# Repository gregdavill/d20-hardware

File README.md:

# d20-hardware
Hardware design files for the icosahedron d20 build.

Read the blog post to read more about the project: https://gregdavill.com/blog/d20

## Assembly BOM
 - 1x d20-control PCBA
 - 20x d20-tri PCBA
 - 20x 6P 0.5mm FFC, 50mm length, opposite side
 - 1x d20_enclosure_r0.1_001.stl
 - 1x d20_enclosure_r0.1_002.stl
 - 1x Sony NP-FW50 battery (knock-offs work fine)

## PCBs

Please use version r0.3 of the d20-tri boards, the earlier versions have severe errata.

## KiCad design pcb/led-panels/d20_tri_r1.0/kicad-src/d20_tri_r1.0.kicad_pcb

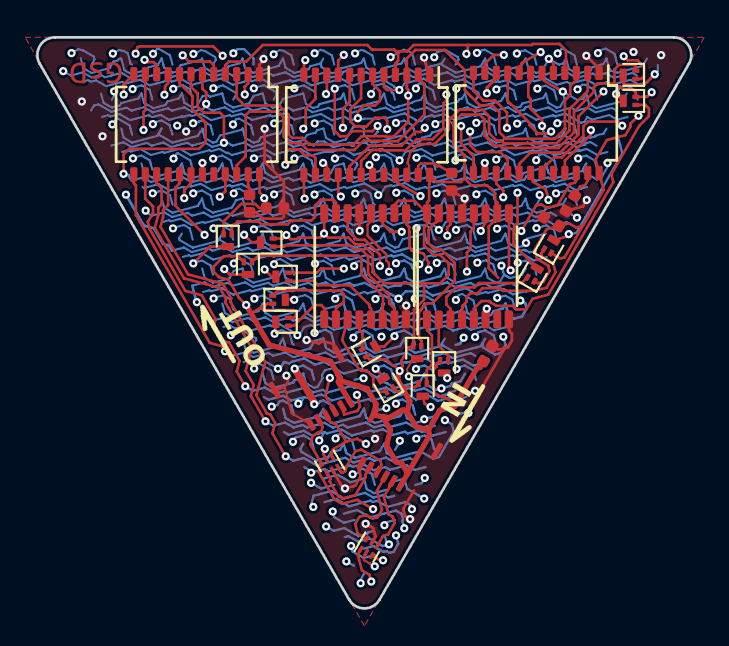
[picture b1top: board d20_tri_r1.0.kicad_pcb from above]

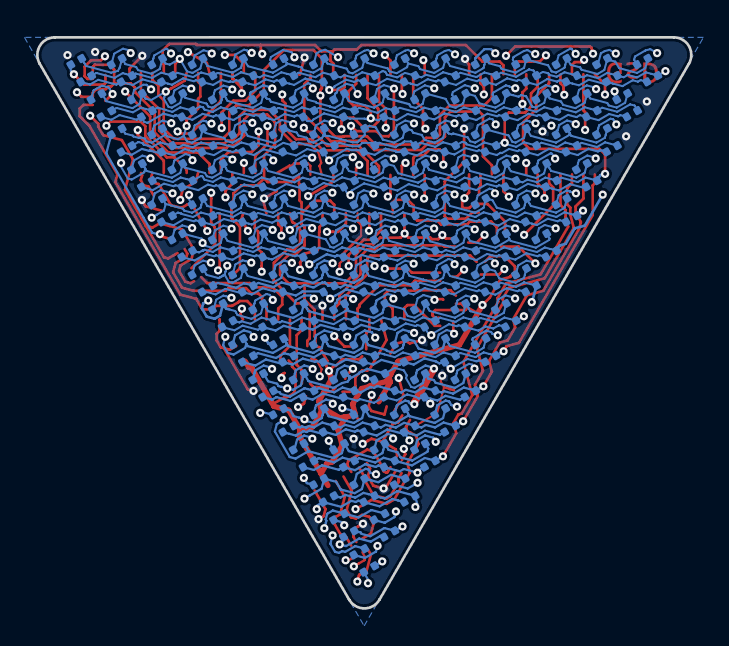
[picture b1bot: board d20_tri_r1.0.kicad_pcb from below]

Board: 4 copper layers, 36.3 x 31.7 mm, 150 parts (120 on the bottom side), 93 nets.

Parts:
C1, C2, C3: 100nF; C_0402_1005Metric
D1, D2, D3, D4, D5, D6, D7, D8, D9, D10, D11, D12, D13, D14, D15, D17, D18, D19, D20, D21, D22, D23, D24, D25, D26, D27, D28, D29, D30, D33, D34, D35, D36, D37, D38, D39, D40, D41, D42, D43, D44, D45, D49, D50, D51, D52, D53, D54, D55, D56, D57, D58, D59, D60, D65, D66, D67, D68, D69, D70, D71, D72, D73, D74, D75, D81, D82, D83, D84, D85, D86, D87, D88, D89, D90, D97, D98, D99, D100, D101, D102, D103, D104, D105, D113, D114, D115, D116, D117, D118, D119, D120, D129, D130, D131, D132, D133, D134, D135, D145, D146, D147, D148, D149, D150, D161, D162, D163, D164, D165, D177, D178, D179, D180, D193, D194, D195, D209, D210, D225: LED_ARGB; led_rbag_1515
J1: input; 5034800600
J2: output; 5034800600
Q1, Q2, Q3, Q4, Q5, Q6, Q7, Q8, Q9, Q10, Q11, Q12, Q13, Q14, Q15: LP0404N3T5G; SOT-883
R1: 2.2k; R_0402_1005Metric
R2: 7.5k; R_0402_1005Metric
R3: 4.12k; R_0402_1005Metric
U1, U2, U3: TLC59025; SSOP-24_slim
U4, U5: 74HC595; TSSOP-16_slim
U6, U7: NC7WZ17; UDFN-6_1x1mm_P0.35mm

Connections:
U1_r_ext: R1.1, U1.23
U2_r_ext: R2.1, U2.23
U3_r_ext: R3.1, U3.23
blank: J2.3, U1.21, U2.21, U3.21, U6.4
blank_i: J1.3, U6.3
colb_0: D1.2, D17.2, D33.2, D49.2, D65.2, D81.2, D97.2, D113.2, D129.2, D145.2, D161.2, D177.2, D193.2, D209.2, D225.2, U3.5
colb_1: D2.2, D18.2, D34.2, D50.2, D66.2, D82.2, D98.2, D114.2, D130.2, D146.2, D162.2, D178.2, D194.2, D210.2, U3.6
colb_2: D3.2, D19.2, D35.2, D51.2, D67.2, D83.2, D99.2, D115.2, D131.2, D147.2, D163.2, D179.2, D195.2, U3.7
colb_3: D4.2, D20.2, D36.2, D52.2, D68.2, D84.2, D100.2, D116.2, D132.2, D148.2, D164.2, D180.2, U3.8
colb_4: D5.2, D21.2, D37.2, D53.2, D69.2, D85.2, D101.2, D117.2, D133.2, D149.2, D165.2, U3.9
colb_5: D6.2, D22.2, D38.2, D54.2, D70.2, D86.2, D102.2, D118.2, D134.2, D150.2, U3.10
colb_6: D7.2, D23.2, D39.2, D55.2, D71.2, D87.2, D103.2, D119.2, D135.2, U3.11
colb_7: D8.2, D24.2, D40.2, D56.2, D72.2, D88.2, D104.2, D120.2, U3.12
colb_8: D9.2, D25.2, D41.2, D57.2, D73.2, D89.2, D105.2, U3.13
colb_9: D10.2, D26.2, D42.2, D58.2, D74.2, D90.2, U3.14
colb_10: D11.2, D27.2, D43.2, D59.2, D75.2, U3.15
colb_11: D12.2, D28.2, D44.2, D60.2, U3.16
colb_12: D13.2, D29.2, D45.2, U3.17
colb_13: D14.2, D30.2, U3.18
colb_14: D15.2, U3.19
colg_0: D1.3, D17.3, D33.3, D49.3, D65.3, D81.3, D97.3, D113.3, D129.3, D145.3, D161.3, D177.3, D193.3, D209.3, D225.3, U2.5
colg_1: D2.3, D18.3, D34.3, D50.3, D66.3, D82.3, D98.3, D114.3, D130.3, D146.3, D162.3, D178.3, D194.3, D210.3, U2.6
colg_2: D3.3, D19.3, D35.3, D51.3, D67.3, D83.3, D99.3, D115.3, D131.3, D147.3, D163.3, D179.3, D195.3, U2.7
colg_3: D4.3, D20.3, D36.3, D52.3, D68.3, D84.3, D100.3, D116.3, D132.3, D148.3, D164.3, D180.3, U2.8
colg_4: D5.3, D21.3, D37.3, D53.3, D69.3, D85.3, D101.3, D117.3, D133.3, D149.3, D165.3, U2.9
colg_5: D6.3, D22.3, D38.3, D54.3, D70.3, D86.3, D102.3, D118.3, D134.3, D150.3, U2.10
colg_6: D7.3, D23.3, D39.3, D55.3, D71.3, D87.3, D103.3, D119.3, D135.3, U2.11
colg_7: D8.3, D24.3, D40.3, D56.3, D72.3, D88.3, D104.3, D120.3, U2.12
colg_8: D9.3, D25.3, D41.3, D57.3, D73.3, D89.3, D105.3, U2.13
colg_9: D10.3, D26.3, D42.3, D58.3, D74.3, D90.3, U2.14
colg_10: D11.3, D27.3, D43.3, D59.3, D75.3, U2.15
colg_11: D12.3, D28.3, D44.3, D60.3, U2.16
colg_12: D13.3, D29.3, D45.3, U2.17
colg_13: D14.3, D30.3, U2.18
colg_14: D15.3, U2.19
colr_0: D1.4, D17.4, D33.4, D49.4, D65.4, D81.4, D97.4, D113.4, D129.4, D145.4, D161.4, D177.4, D193.4, D209.4, D225.4, U1.5
colr_1: D2.4, D18.4, D34.4, D50.4, D66.4, D82.4, D98.4, D114.4, D130.4, D146.4, D162.4, D178.4, D194.4, D210.4, U1.6
colr_2: D3.4, D19.4, D35.4, D51.4, D67.4, D83.4, D99.4, D115.4, D131.4, D147.4, D163.4, D179.4, D195.4, U1.7
colr_3: D4.4, D20.4, D36.4, D52.4, D68.4, D84.4, D100.4, D116.4, D132.4, D148.4, D164.4, D180.4, U1.8
colr_4: D5.4, D21.4, D37.4, D53.4, D69.4, D85.4, D101.4, D117.4, D133.4, D149.4, D165.4, U1.9
colr_5: D6.4, D22.4, D38.4, D54.4, D70.4, D86.4, D102.4, D118.4, D134.4, D150.4, U1.10
colr_6: D7.4, D23.4, D39.4, D55.4, D71.4, D87.4, D103.4, D119.4, D135.4, U1.11
colr_7: D8.4, D24.4, D40.4, D56.4, D72.4, D88.4, D104.4, D120.4, U1.12
colr_8: D9.4, D25.4, D41.4, D57.4, D73.4, D89.4, D105.4, U1.13
colr_9: D10.4, D26.4, D42.4, D58.4, D74.4, D90.4, U1.14
colr_10: D11.4, D27.4, D43.4, D59.4, D75.4, U1.15
colr_11: D12.4, D28.4, D44.4, D60.4, U1.16
colr_12: D13.4, D29.4, D45.4, U1.17
colr_13: D14.4, D30.4, U1.18
colr_14: D15.4, U1.19
dat: U1.2, U6.6
dat_i: J1.2, U6.1
dat_out: J2.2, U5.9
gnd: C1.2, C2.2, C3.2, J1.6, J1.SH, J2.6, J2.SH, R1.2, R2.2, R3.2, U1.1, U2.1, U3.1, U4.8, U4.13, U5.8, U5.13, U6.2, U7.2
latch: J2.4, U1.4, U2.4, U3.4, U4.12, U5.12, U7.4
latch_i: J1.4, U7.3
row_0: D1.1, D2.1, D3.1, D4.1, D5.1, D6.1, D7.1, D8.1, D9.1, D10.1, D11.1, D12.1, D13.1, D14.1, D15.1, Q1.3
row_1: D17.1, D18.1, D19.1, D20.1, D21.1, D22.1, D23.1, D24.1, D25.1, D26.1, D27.1, D28.1, D29.1, D30.1, Q2.3
row_2: D33.1, D34.1, D35.1, D36.1, D37.1, D38.1, D39.1, D40.1, D41.1, D42.1, D43.1, D44.1, D45.1, Q3.3
row_3: D49.1, D50.1, D51.1, D52.1, D53.1, D54.1, D55.1, D56.1, D57.1, D58.1, D59.1, D60.1, Q4.3
row_4: D65.1, D66.1, D67.1, D68.1, D69.1, D70.1, D71.1, D72.1, D73.1, D74.1, D75.1, Q5.3
row_5: D81.1, D82.1, D83.1, D84.1, D85.1, D86.1, D87.1, D88.1, D89.1, D90.1, Q6.3
row_6: D97.1, D98.1, D99.1, D100.1, D101.1, D102.1, D103.1, D104.1, D105.1, Q7.3
row_7: D113.1, D114.1, D115.1, D116.1, D117.1, D118.1, D119.1, D120.1, Q8.3
row_8: D129.1, D130.1, D131.1, D132.1, D133.1, D134.1, D135.1, Q9.3
row_9: D145.1, D146.1, D147.1, D148.1, D149.1, D150.1, Q10.3
row_10: D161.1, D162.1, D163.1, D164.1, D165.1, Q11.3
row_11: D177.1, D178.1, D179.1, D180.1, Q12.3
row_12: D193.1, D194.1, D195.1, Q13.3
row_13: D209.1, D210.1, Q14.3
row_14: D225.1, Q15.3
sclk: J2.5, U1.3, U2.3, U3.3, U4.11, U5.11, U7.6
sclk_i: J1.5, U7.1
sdo_U1>sdi_U2: U1.22, U2.2
sdo_U2>sdi_U3: U2.22, U3.2
sdo_U3: U3.22, U4.14
sdo_U4>sdi_U5: U4.9, U5.14
srow_0: Q1.1, U4.15
srow_1: Q2.1, U4.1
srow_2: Q3.1, U4.2
srow_3: Q4.1, U4.3
srow_4: Q5.1, U4.4
srow_5: Q6.1, U4.5
srow_6: Q7.1, U4.6
srow_7: Q8.1, U4.7
srow_8: Q9.1, U5.15
srow_9: Q10.1, U5.1
srow_10: Q11.1, U5.2
srow_11: Q12.1, U5.3
srow_12: Q13.1, U5.4
srow_13: Q14.1, U5.5
srow_14: Q15.1, U5.6
vcc: C1.1, C2.1, C3.1, J1.1, J1.SH, J2.1, Q1.2, Q2.2, Q3.2, Q4.2, Q5.2, Q6.2, Q7.2, Q8.2, Q9.2, Q10.2, Q11.2, Q12.2, Q13.2, Q14.2, Q15.2, U1.24, U2.24, U3.24, U4.10, U4.16, U5.10, U5.16, U6.5, U7.5

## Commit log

2021-03-29 Add initial design files
2021-03-30 Add step model
2021-03-30 docs: Update readme
2021-05-08 Remove old STEP file
2021-05-08 Add .gitattributes
2021-05-08 Add new STEP/f3d models
2021-06-24 Correct small spelling mistake in README.md
2021-06-24 Add kitspace.yaml
2021-06-30 git move lfs to git
2021-06-30 update gitattributes
2022-06-24 pcb: Add inital r1.0 panel design
2022-06-24 Add basic BOM output script
2022-06-25 pcb: Update skidl script
2022-06-25 pcb: Update design
    - Add Libs
    - Fix ERC errors
    - Update config
2022-06-25 pcb: Update script
2022-06-25 pcb: Update layout
